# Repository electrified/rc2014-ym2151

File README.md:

# OPM Tone Generator (AKA YM2151 Sound card) for RC2014/RC40 bus computers

## The board
RC40 bus OPM FM Sound card.

## Features
- FM Operator Type M (OPM)
- 4 operators
- 8 algorithms
- 8 notes
- Stereo output

## History
The YM2151 tone generator and accompanying YM3012 stereo DAC have been used in several computer systems.
Most notably the Sharp X68000 and Yamaha's CX5M MSX computer, along with a number of arcade boards.
More recently the retro inspired Commander X16 currently has one in it's design.

Yamaha's DX21, DX27 and DX100 synthesisers used a derivative IC which is very similar.

## What music files can be played back?
- YM2151 VGM files (using vgmplayer)
- Sharp X68000 MDX files (using mdxplay https://github.com/electrified/mdxplay-rc2014)

## Bill Of Materials
Download the latest Documentation zip from the releases section. This contains a HTML iBOM in the BOM folder.

## Gerbers
Download the latest JLCPCB zip from the releases section. This contains standard Gerbers.

## Sources / attribution
Beep program modified from https://commander-cx16.fandom.com/wiki/Beep

vgmplayer modified from Marco's version at https://groups.google.com/g/rc2014-z80/c/9nHnETJzGKU/m/z1A33J_GBAAJ, in turn modified from jblang's version at https://github.com/jblang/SN76489/blob/master/examples/vgmplayer.asm

KiCad Github actions
https://github.com/INTI-CMNB/kibot
https://github.com/neilenns/KiBot-CICD-Template
https://github.com/neilenns/CJ4-Electrical-Panel

## Background reading/ viewing
https://ayce.dev/emptyx16.html#9f41h---ym2151-register-data-w--status-r

https://ayce.dev/emptyx16.html#ym2151-fm-operator-type-m-opm

https://www.youtube.com/watch?v=BG6q53p7Z10

https://www.youtube.com/watch?v=GnbT23wGcIA

https://www.youtube.com/watch?v=C8K_VtGyjHM

https://vgmrips.net/wiki/OPM_File_Format

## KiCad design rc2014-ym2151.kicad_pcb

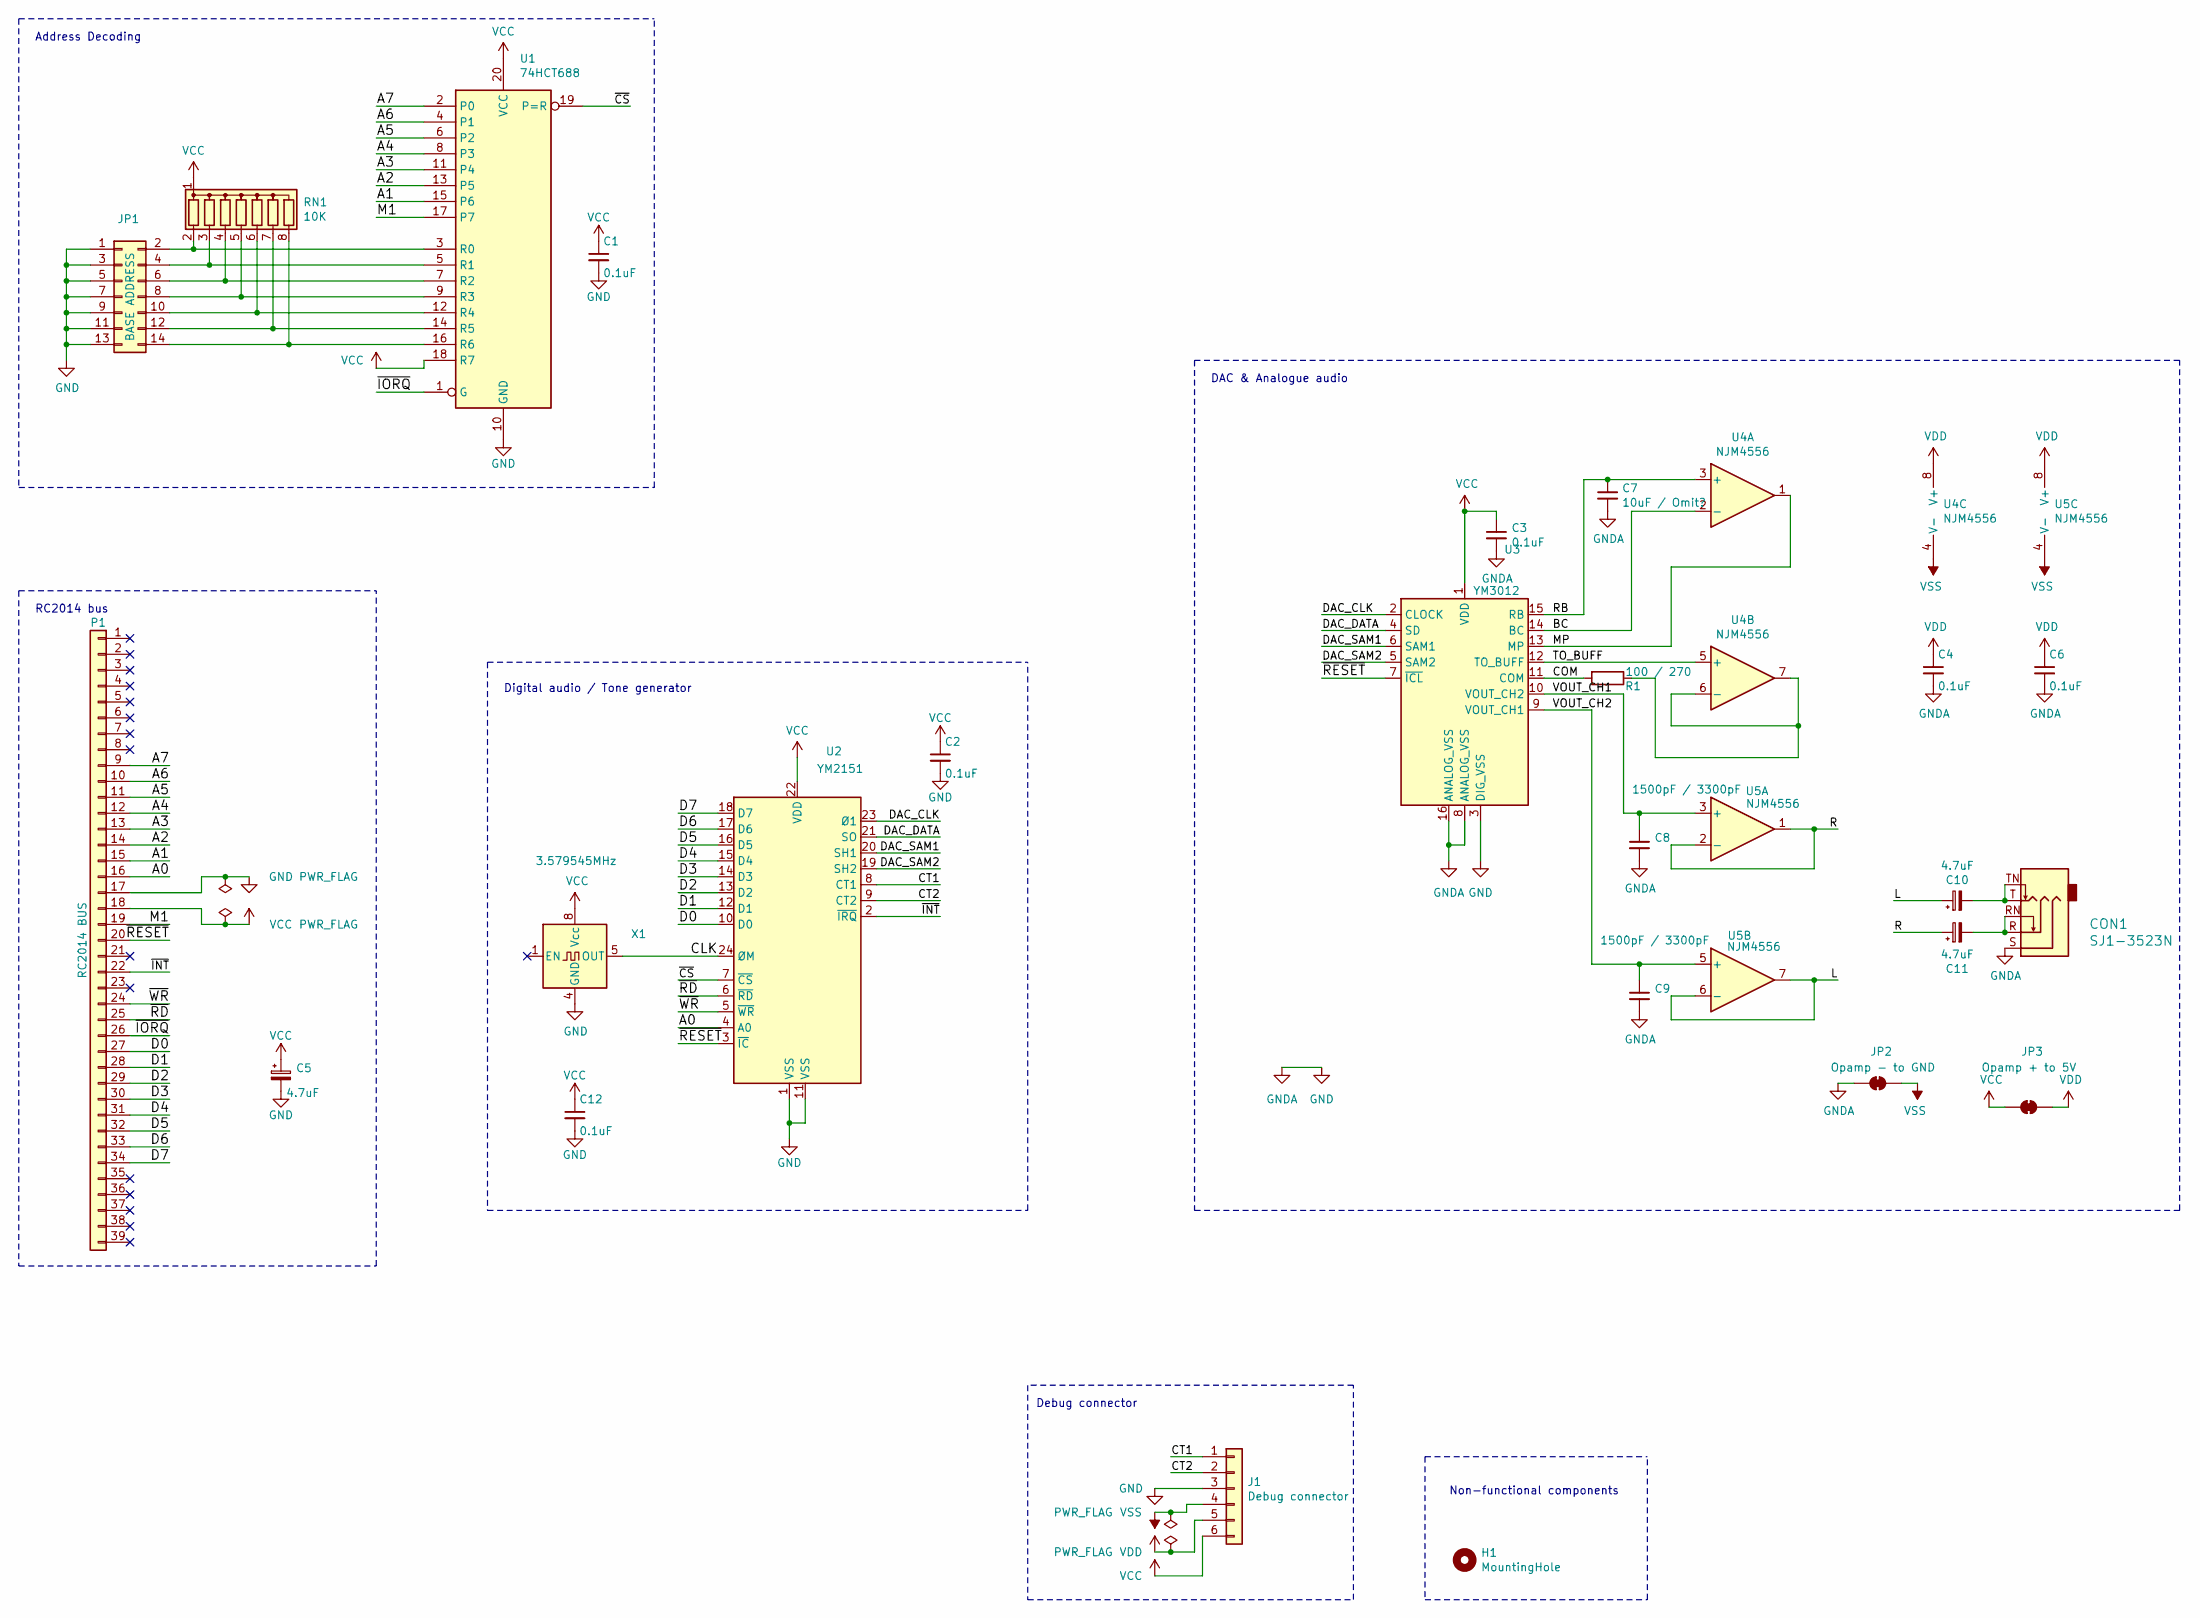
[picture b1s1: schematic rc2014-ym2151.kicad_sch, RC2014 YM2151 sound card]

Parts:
C1, C2, C3, C4, C6, C12: 0.1uF; C_Disc_D3.8mm_W2.6mm_P2.50mm
C5: 4.7uF; CP_Radial_D7.5mm_P2.50mm
C7: 10uF / Omit?; C_Radial_D4.0mm_H7.0mm_P1.50mm
C8, C9: 1500pF / 3300pF; C_Disc_D3.8mm_W2.6mm_P2.50mm
C10, C11: 4.7uF; CP_Radial_D5.0mm_P2.50mm
CON1: SJ1-3523N; Headphone_Jack_3.5mm_5_pin; MPN SJ1-3523N; Digi-Key_PN CP1-3523N-ND
H1: MountingHole; MountingHole_3.2mm_M3
J1: Debug connector; PinHeader_1x06_P2.54mm_Vertical
JP1: BASE ADDRESS; PinHeader_2x07_P2.54mm_Vertical
JP2: Opamp - to GND; SolderJumper-2_P1.3mm_Bridged2Bar_RoundedPad1.0x1.5mm
JP3: Opamp + to 5V; SolderJumper-2_P1.3mm_Bridged2Bar_RoundedPad1.0x1.5mm
P1: RC2014 BUS; PinHeader_1x39_P2.54mm_Vertical
R1: 100 / 270; R_Axial_DIN0204_L3.6mm_D1.6mm_P7.62mm_Horizontal
RN1: 10K; R_Array_SIP8
U1: 74HCT688; DIP-20_W7.62mm_Socket
U2: YM2151; DIP-24_W15.24mm
U3: YM3012; DIP-16_W7.62mm
U4, U5: NJM4556; DIP-8_W7.62mm_Socket
X1: 3.579545MHz; DIP-8_W7.62mm_Socket

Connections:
/A0: P1.16, U2.4 (A0)
/A1: P1.15, U1.15 (P6)
/A2: P1.14, U1.13 (P5)
/A3: P1.13, U1.11 (P4)
/A4: P1.12, U1.8 (P3)
/A5: P1.11, U1.6 (P2)
/A6: P1.10, U1.4 (P1)
/A7: P1.9, U1.2 (P0)
/BC: U3.14 (BC), U4.2 (-)
/CLK: U2.24 (ØM), X1.5 (OUT)
/COM: R1.2, U3.11 (COM)
/CT1: J1.1, U2.8 (CT1)
/CT2: J1.2, U2.9 (CT2)
/D0: P1.27, U2.10 (D0)
/D1: P1.28, U2.12 (D1)
/D2: P1.29, U2.13 (D2)
/D3: P1.30, U2.14 (D3)
/D4: P1.31, U2.15 (D4)
/D5: P1.32, U2.16 (D5)
/D6: P1.33, U2.17 (D6)
/D7: P1.34, U2.18 (D7)
/DAC_CLK: U2.23 (Ø1), U3.2 (CLOCK)
/DAC_DATA: U2.21 (SO), U3.4 (SD)
/DAC_SAM1: U2.20 (SH1), U3.6 (SAM1)
/DAC_SAM2: U2.19 (SH2), U3.5 (SAM2)
/L: C10.1, U5.6 (-), U5.7
/M1: P1.19, U1.17 (P7)
/MP: U3.13 (MP), U4.1
/R: C11.1, U5.1, U5.2 (-)
/RB: C7.1, U3.15 (RB), U4.3 (+)
/TO_BUFF: U3.12 (TO_BUFF), U4.5 (+)
/VOUT_CH1: C8.1, U3.10 (VOUT_CH2), U5.3 (+)
/VOUT_CH2: C9.1, U3.9 (VOUT_CH1), U5.5 (+)
/~CS: U1.19 (P=R), U2.7 (~CS)
/~INT: P1.22, U2.2 (~IRQ)
/~IORQ: P1.26, U1.1 (G)
/~RD: P1.25, U2.6 (~RD)
/~RESET: P1.20, U2.3 (~IC), U3.7 (~ICL)
/~WR: P1.24, U2.5 (~WR)
GND: C1.2, C2.2, C3.2, C4.2, C5.2, C6.2, C7.2, C8.2, C9.2, C12.2, CON1.S, J1.3, JP1.1, JP1.3, JP1.5, JP1.7, JP1.9, JP1.11, JP1.13, JP2.1 (A), P1.17, U1.10 (GND), U2.1 (VSS), U2.11 (VSS), U3.3 (DIG_VSS), U3.8 (ANALOG_VSS), U3.16 (ANALOG_VSS), X1.4 (GND)
unnamed: C10.2, CON1.T, CON1.TN
unnamed: C11.2, CON1.R, CON1.RN
unnamed: JP1.2, RN1.2 (R1), U1.3 (R0)
unnamed: JP1.4, RN1.3 (R2), U1.5 (R1)
unnamed: JP1.6, RN1.4 (R3), U1.7 (R2)
unnamed: JP1.8, RN1.5 (R4), U1.9 (R3)
unnamed: JP1.10, RN1.6 (R5), U1.12 (R4)
unnamed: JP1.12, RN1.7 (R6), U1.14 (R5)
unnamed: JP1.14, RN1.8 (R7), U1.16 (R6)
unnamed: R1.1, U4.6 (-), U4.7
VCC: C1.1, C2.1, C3.1, C5.1, C12.1, J1.6, JP3.1 (A), P1.18, RN1.1 (common), U1.18 (R7), U1.20 (VCC), U2.22 (VDD), U3.1 (VDD), X1.8 (Vcc)
VDD: C4.1, C6.1, J1.5, JP3.2 (B), U4.8 (V+), U5.8 (V+)
VSS: J1.4, JP2.2 (B), U4.4 (V-), U5.4 (V-)

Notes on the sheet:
Non-functional components
Digital audio / Tone generator
Debug connector
Address Decoding
DAC & Analogue audio
RC2014 bus

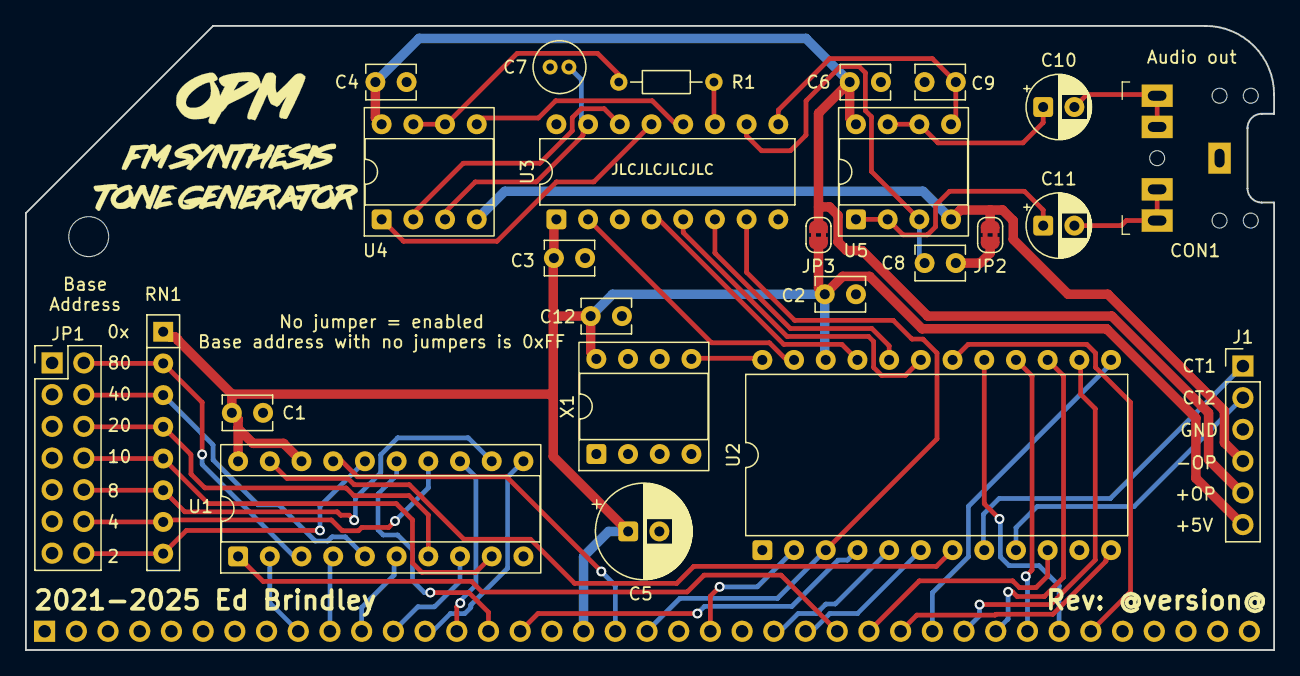
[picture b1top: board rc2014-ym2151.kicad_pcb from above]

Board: 2 copper layers, 100.0 x 50.0 mm, 29 parts (1 on the bottom side), 53 nets.

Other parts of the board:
G1: LOGO; opm
G3: OSHW-Logo_11.4x12mm_SilkScreen

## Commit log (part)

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2021-11-09 First version that looks reasonable....
2021-11-09 Add actions gerber build
2021-11-11 Use git submode for library
2021-11-11 submodules round 2
2021-11-16 Fix up silkscreen, move opamp location slightly
2021-11-19 Add ability to power opamps separately
2021-11-20 further updates
2021-11-20 Move some component references
2021-11-20 Switch to using KiBot-CICD-Template
2021-11-20 submodules
2021-11-20 hardcode pcb date
2021-11-20 Attempt fix
2021-11-20 add date palaceholder back
2021-11-20 Don't write out time
2021-11-20 move version tag
2021-11-21 Tidy schematic and readme
2021-11-24 Update build script to latest released version, and PCB missed from previous commit
2021-11-27 Add unmodified vgmplay
2021-11-28 software WIP
2021-11-29 Build with gcc for testing
2021-12-17 add bits lurking around
2021-12-31 Update to Kicad 6
2022-01-09 schematic tidyup
2022-02-21 Tidy up schematic further
2022-02-21 Update sch paths to use kicad 6 extension
2022-02-21 Attempt at getting github actions working
2022-02-21 Update kibot template
2022-02-21 change kibot action version in release workflow
2022-02-21 Fix indentation
2022-02-21 attempt to fix date replacement
2022-02-21 remove silk that clashes, another date fix
2022-02-21 date fix
2022-02-22 Use date and versioning built into kibot
2022-02-22 date replacement
2022-02-28 Use Aisler DRC
    Update README.md
    change board outline
    wip
2022-03-02 remove dubious silkscreen
2025-07-01 kicad 9 work in progress
2025-07-01 migrate to kicad 9 - fix most of the ERC and DRC issues, use current library symbols/footprints
2025-07-01 Bump actions/upload-artifact from 2 to 4
    Bumps [actions/upload-artifact](https://github.com/actions/upload-artifact) from 2 to 4.
    - [Release notes](https://github.com/actions/upload-artifact/releases)
    - [Commits](https://github.com/actions/upload-artifact/compare/v2...v4)
    ---
    updated-dependencies:
    - dependency-name: actions/upload-artifact
2025-07-01 Bump actions/checkout from 2 to 4
    Bumps [actions/checkout](https://github.com/actions/checkout) from 2 to 4.
    - [Release notes](https://github.com/actions/checkout/releases)
    - [Changelog](https://github.com/actions/checkout/blob/main/CHANGELOG.md)
    - [Commits](https://github.com/actions/checkout/compare/v2...v4)
    ---
    updated-dependencies:
2025-07-01 Bump softprops/action-gh-release from 1 to 2
    Bumps [softprops/action-gh-release](https://github.com/softprops/action-gh-release) from 1 to 2.
    - [Release notes](https://github.com/softprops/action-gh-release/releases)
    - [Changelog](https://github.com/softprops/action-gh-release/blob/master/CHANGELOG.md)
    - [Commits](https://github.com/softprops/action-gh-release/compare/v1...v2)
    ---
    updated-dependencies:
2025-07-01 Bump the actions-dependencies group with 3 updates
    Bumps the actions-dependencies group with 3 updates: [actions/checkout](https://github.com/actions/checkout), [actions/upload-artifact](https://github.com/actions/upload-artifact) and [softprops/acti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
    Updates `actions/checkout` from 2 to 4
    - [Release notes](https://github.com/actions/checkout/releases)
    - [Changelog](https://github.com/actions/checkout/blob/main/CHANGELOG.md)
    - [Commits](https://github.com/actions/checkout/compare/v2...v4)
    Updates `actions/upload-artifact` from 2 to 4
2025-07-01 update kibot
2025-07-01 update copyright date
2025-07-01 add manual trigger for prerelease
2025-07-01 update kibot config
2025-07-20 kicad 9 updates
2025-08-11 Bump actions/checkout from 4 to 5 in the actions-dependencies group
    Bumps the actions-dependencies group with 1 update: [actions/checkout](https://github.com/actions/checkout).
    Updates `actions/checkout` from 4 to 5
    - [Release notes](https://github.com/actions/checkout/releases)
    - [Changelog](https://github.com/actions/checkout/blob/main/CHANGELOG.md)
    - [Commits](https://github.com/actions/checkout/compare/v4...v5)
    ---
2025-10-27 Bump the actions-dependencies group across 1 directory with 2 updates
    Bumps the actions-dependencies group with 2 updates in the / directory: [actions/checkout](https://github.com/actions/checkout) and [actions/upload-artifact](https://github.com/actions/upload-artifac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
    Updates `actions/checkout` from 4 to 5
    - [Release notes](https://github.com/actions/checkout/releases)
    - [Changelog](https://github.com/actions/checkout/blob/main/CHANGELOG.md)
    - [Commits](https://github.com/actions/checkout/compare/v4...v5)
    Updates `actions/upload-artifact` from 4 to 5
2026-04-13 Bump the actions-dependencies group across 1 directory with 3 updates
    Bumps the actions-dependencies group with 3 updates in the / directory: [actions/checkout](https://github.com/actions/checkout), [actions/upload-artifact](https://github.com/actions/upload-artifact) 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
    Updates `actions/checkout` from 4 to 6
    - [Release notes](https://github.com/actions/checkout/releases)
    - [Changelog](https://github.com/actions/checkout/blob/main/CHANGELOG.md)
    - [Commits](https://github.com/actions/checkout/compare/v4...v6)
    Updates `actions/upload-artifact` from 4 to 7
